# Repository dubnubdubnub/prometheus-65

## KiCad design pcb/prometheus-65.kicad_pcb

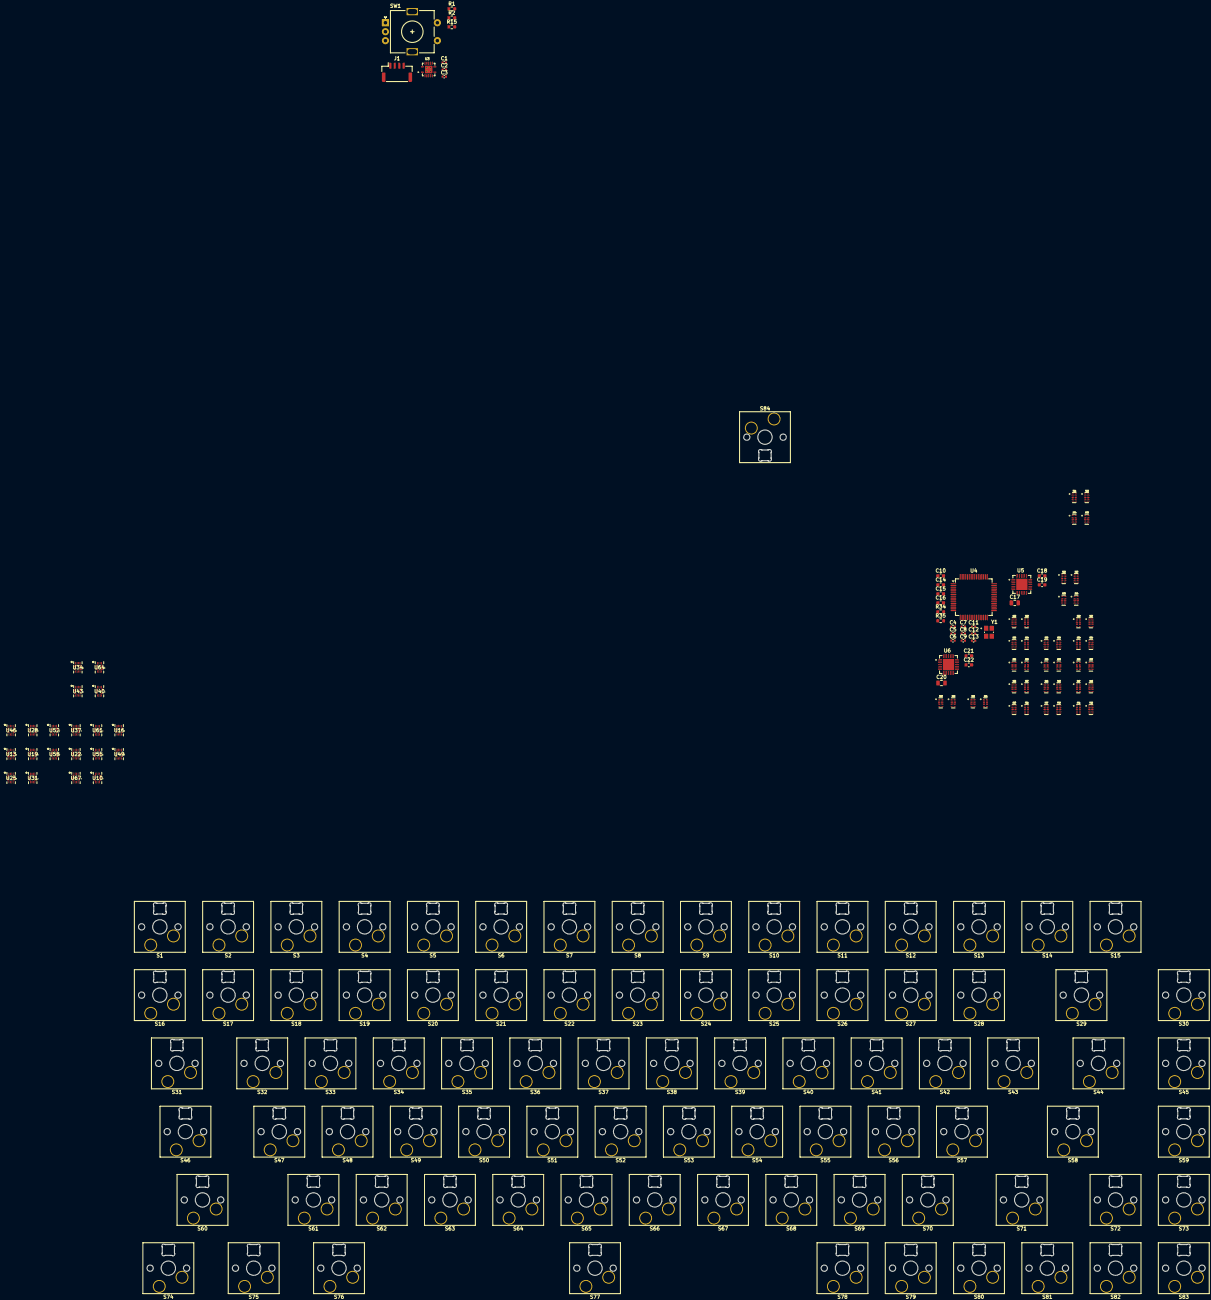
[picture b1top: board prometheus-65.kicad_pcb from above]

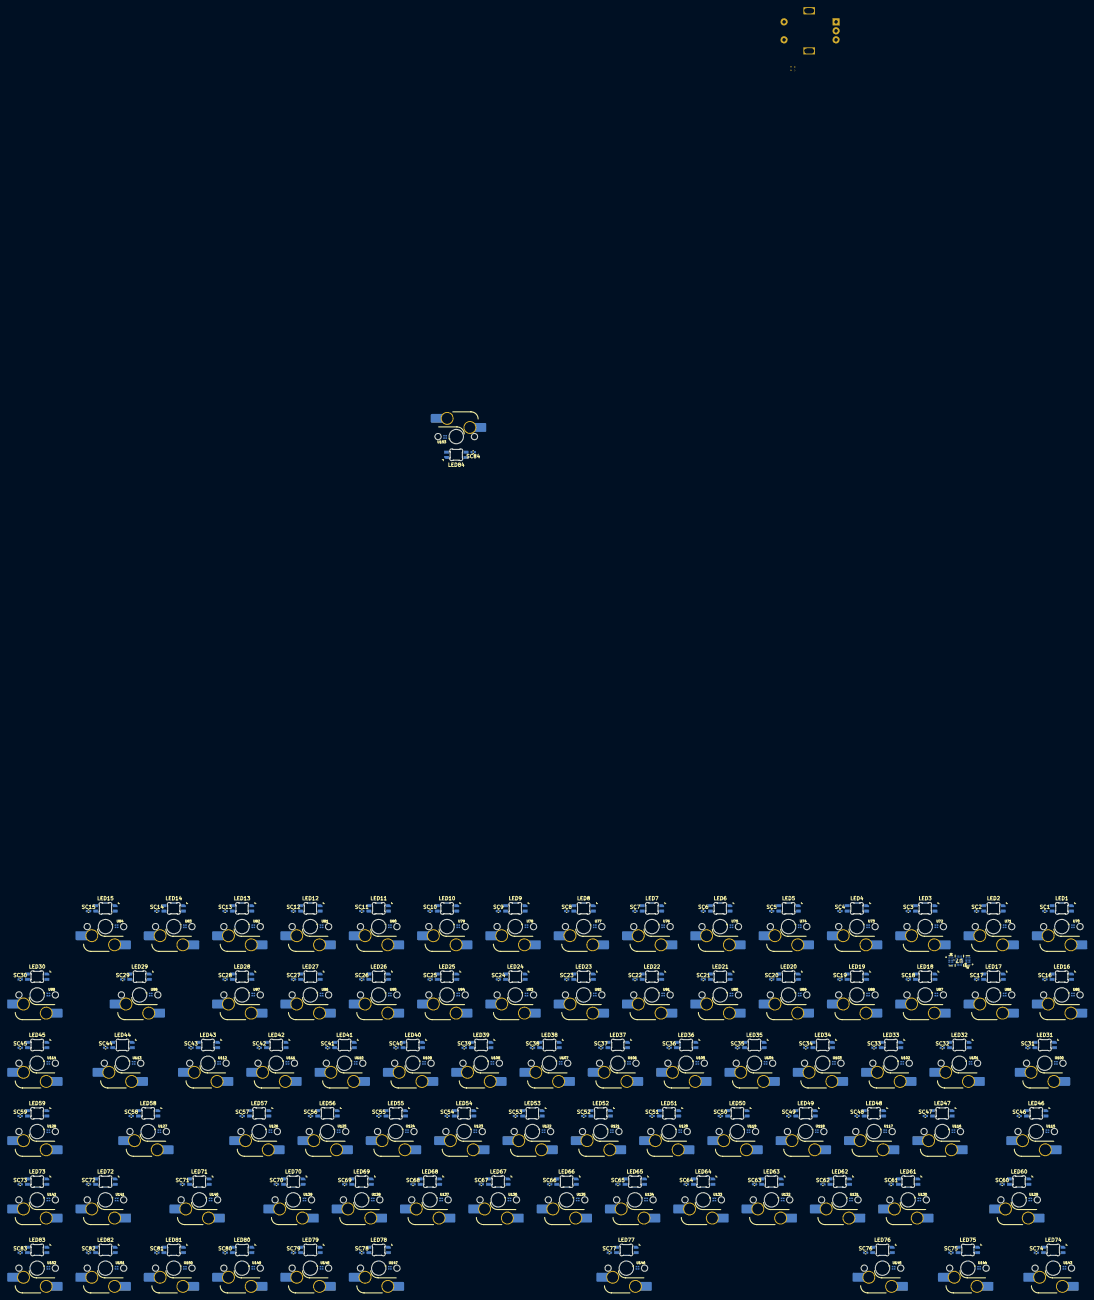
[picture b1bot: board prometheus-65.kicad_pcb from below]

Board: 6 copper layers, 433 parts (255 on the bottom side), 373 nets, no tracks yet.

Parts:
C1, C2, C3, C4, C5, C6, C7, C8, C9, C11: 100nF; C_0402_1005Metric
C10: 4.7uF; C_0603_1608Metric
C12, C13: 22pF; C_0402_1005Metric
C14, C15: 2.2uF; C_0603_1608Metric
C16, C19, C22: 1uF; C_0603_1608Metric
C17, C20: 47uF; C_0805_2012Metric
C18, C21: 10uF; C_0603_1608Metric
J1: Conn_01x04_Socket; JST_GH_SM04B-GHS-TB_1x04-1MP_P1.25mm_Horizontal
LED1, LED2, LED3, LED4, LED5, LED6, LED7, LED8, LED9, LED10, LED11, LED12, LED13, LED14, LED15, LED16, LED17, LED18, LED19, LED20, LED21, LED22, LED23, LED24, LED25, LED26, LED27, LED28, LED29, LED30, LED31, LED32, LED33, LED34, LED35, LED36, LED37, LED38, LED39, LED40, LED41, LED42, LED43, LED44, LED45, LED46, LED47, LED48, LED49, LED50, LED51, LED52, LED53, LED54, LED55, LED56, LED57, LED58, LED59, LED60, LED61, LED62, LED63, LED64, LED65, LED66, LED67, LED68, LED69, LED70, LED71, LED72, LED73, LED74, LED75, LED76, LED77, LED78, LED79, LED80, LED81, LED82, LED83, LED84: SK6812MINI-E; LED_6028R
R1, R2: 22Ω; R_0603_1608Metric
R15: 330Ω; R_0603_1608Metric
R34, R35: 10kΩ; R_0603_1608Metric
S1, S2, S3, S4, S5, S6, S7, S8, S9, S10, S11, S12, S13, S14, S15, S16, S17, S18, S19, S20, S21, S22, S23, S24, S25, S26, S27, S28, S29, S30, S31, S32, S33, S34, S35, S36, S37, S38, S39, S40, S41, S42, S43, S44, S45, S46, S47, S48, S49, S50, S51, S52, S53, S54, S55, S56, S57, S58, S59, S60, S61, S62, S63, S64, S65, S66, S67, S68, S69, S70, S71, S72, S73, S74, S75, S76, S77, S78, S79, S80, S81, S82, S83, S84: 1.00u; Hotswap_MX_Plated_1.00u
SC1, SC2, SC3, SC4, SC5, SC6, SC7, SC8, SC9, SC10, SC11, SC12, SC13, SC14, SC15, SC16, SC17, SC18, SC19, SC20, SC21, SC22, SC23, SC24, SC25, SC26, SC27, SC28, SC29, SC30, SC31, SC32, SC33, SC34, SC35, SC36, SC37, SC38, SC39, SC40, SC41, SC42, SC43, SC44, SC45, SC46, SC47, SC48, SC49, SC50, SC51, SC52, SC53, SC54, SC55, SC56, SC57, SC58, SC59, SC60, SC61, SC62, SC63, SC64, SC65, SC66, SC67, SC68, SC69, SC70, SC71, SC72, SC73, SC74, SC75, SC76, SC77, SC78, SC79, SC80, SC81, SC82, SC83, SC84: 100nF; C_0402_1005Metric
SW1: RotaryEncoder_Switch; RotaryEncoder_Alps_EC11E-Switch_Vertical_H20mm
U3: 74AHCT125; SN74AUC08RGYRG4
U4: STM32F405RGTx; LQFP-64_10x10mm_P0.5mm
U5, U6: TPS7A4700; TPS7A47000RGWT
U7, U10, U13, U16, U19, U22, U25, U28, U31, U34, U37, U40, U43, U46, U49, U52, U55, U58, U61, U64, U67: TMUX1109RSVR
U8, U9, U11, U12, U14, U15, U17, U18, U20, U21, U23, U24, U26, U27, U29, U30, U32, U33, U35, U36, U38, U39, U41, U42, U44, U45, U47, U48, U50, U51, U53, U54, U56, U57, U59, U60, U62, U63, U65, U66, U68, U69: TPD4E05U06DQAR
U70, U71, U72, U73, U74, U75, U76, U77, U78, U79, U80, U81, U82, U83, U84, U85, U86, U87, U88, U89, U90, U91, U92, U93, U94, U95, U96, U97, U98, U99, U100, U101, U102, U103, U104, U105, U106, U107, U108, U109, U110, U111, U112, U113, U114, U115, U116, U117, U118, U119, U120, U121, U122, U123, U124, U125, U126, U127, U128, U129, U130, U131, U132, U133, U134, U135, U136, U137, U138, U139, U140, U141, U142, U143, U144, U145, U146, U147, U148, U149, U150, U151, U152, U153: ALT025-14E
Y1: FA-238_16.0000MA20W-C

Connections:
+3.3VA: C1.2, C3.2, C9.2, C16.2, C20.1, U4.13 (VDDA), U6.1 (OUT), U6.3 (SENSE/FB), U6.20 (OUT), U70.2 (VCC), U71.2 (VCC), U72.2 (VCC), U73.2 (VCC), U74.2 (VCC), U75.2 (VCC), U76.2 (VCC), U77.2 (VCC), U78.2 (VCC), U79.2 (VCC), U80.2 (VCC), U81.2 (VCC), U82.2 (VCC), U83.2 (VCC), U84.2 (VCC), U85.2 (VCC), U86.2 (VCC), U87.2 (VCC), U88.2 (VCC), U89.2 (VCC), U90.2 (VCC), U91.2 (VCC), U92.2 (VCC), U93.2 (VCC), U94.2 (VCC), U95.2 (VCC), U96.2 (VCC), U97.2 (VCC), U98.2 (VCC), U99.2 (VCC), U100.2 (VCC), U101.2 (VCC), U102.2 (VCC), U103.2 (VCC), U104.2 (VCC), U105.2 (VCC), U106.2 (VCC), U107.2 (VCC), U108.2 (VCC), U109.2 (VCC), U110.2 (VCC), U111.2 (VCC), U112.2 (VCC), U113.2 (VCC), U114.2 (VCC), U115.2 (VCC), U116.2 (VCC), U117.2 (VCC), U118.2 (VCC), U119.2 (VCC), U120.2 (VCC), U121.2 (VCC), U122.2 (VCC), U123.2 (VCC), U124.2 (VCC), U125.2 (VCC), U126.2 (VCC), U127.2 (VCC), U128.2 (VCC), U129.2 (VCC), U130.2 (VCC), U131.2 (VCC), U132.2 (VCC), U133.2 (VCC), U134.2 (VCC), U135.2 (VCC), U136.2 (VCC), U137.2 (VCC), U138.2 (VCC), U139.2 (VCC), U140.2 (VCC), U141.2 (VCC), U142.2 (VCC), U143.2 (VCC), U144.2 (VCC), U145.2 (VCC), U146.2 (VCC), U147.2 (VCC), U148.2 (VCC), U149.2 (VCC), U150.2 (VCC), U151.2 (VCC), U152.2 (VCC), U153.2 (VCC)
+3.3VD: C4.2, C5.2, C6.2, C7.2, C8.2, C10.1, C17.1, R34.2, U4.1 (VBAT), U4.19 (VDD), U4.32 (VDD), U4.48 (VDD), U4.64 (VDD), U5.1 (OUT), U5.3 (SENSE/FB), U5.20 (OUT)
+5V: C18.2, C21.2, J1.1, SC1.1, SC2.1, SC3.1, SC4.1, SC5.1, SC6.1, SC7.1, SC8.1, SC9.1, SC10.1, SC11.1, SC12.1, SC13.1, SC14.1, SC15.1, SC16.1, SC17.1, SC18.1, SC19.1, SC20.1, SC21.1, SC22.1, SC23.1, SC24.1, SC25.1, SC26.1, SC27.1, SC28.1, SC29.1, SC30.1, SC31.1, SC32.1, SC33.1, SC34.1, SC35.1, SC36.1, SC37.1, SC38.1, SC39.1, SC40.1, SC41.1, SC42.1, SC43.1, SC44.1, SC45.1, SC46.1, SC47.1, SC48.1, SC49.1, SC50.1, SC51.1, SC52.1, SC53.1, SC54.1, SC55.1, SC56.1, SC57.1, SC58.1, SC59.1, SC60.1, SC61.1, SC62.1, SC63.1, SC64.1, SC65.1, SC66.1, SC67.1, SC68.1, SC69.1, SC70.1, SC71.1, SC72.1, SC73.1, SC74.1, SC75.1, SC76.1, SC77.1, SC78.1, SC79.1, SC80.1, SC81.1, SC82.1, SC83.1, SC84.1, U3.14 (VCC), U5.13 (EN), U5.15 (IN), U5.16 (IN), U6.13 (EN), U6.15 (IN), U6.16 (IN)
/Key_1/DOUT: LED1.2 (DOUT), LED2.3 (DIN)
/Key_1/OUT+: S1.1, U7.2 (S1A), U8.1 (D1+), U70.1 (OUT+)
/Key_1/OUT-: U7.11 (S1B), U8.2 (D1-), U70.3 (OUT-)
/Key_2/DOUT: LED2.2 (DOUT), LED3.3 (DIN)
/Key_2/OUT+: S2.1, U7.3 (S2A), U8.4 (D2+), U71.1 (OUT+)
/Key_2/OUT-: U7.10 (S2B), U8.5 (D2-), U71.3 (OUT-)
/Key_3/DOUT: LED3.2 (DOUT), LED4.3 (DIN)
/Key_3/OUT+: S3.1, U7.4 (S3A), U9.1 (D1+), U72.1 (OUT+)
/Key_3/OUT-: U7.9 (S3B), U9.2 (D1-), U72.3 (OUT-)
/Key_4/DOUT: LED4.2 (DOUT), LED5.3 (DIN)
/Key_4/OUT+: S4.1, U7.5 (S4A), U9.4 (D2+), U73.1 (OUT+)
/Key_4/OUT-: U7.8 (S4B), U9.5 (D2-), U73.3 (OUT-)
/Key_5/OUT+: S5.1, U10.2 (S1A), U11.1 (D1+), U74.1 (OUT+)
/Key_5/OUT-: U10.11 (S1B), U11.2 (D1-), U74.3 (OUT-)
/Key_6/OUT+: S6.1, U10.3 (S2A), U11.4 (D2+), U75.1 (OUT+)
/Key_6/OUT-: U10.10 (S2B), U11.5 (D2-), U75.3 (OUT-)
/Key_7/OUT+: S7.1, U10.4 (S3A), U12.1 (D1+), U76.1 (OUT+)
/Key_7/OUT-: U10.9 (S3B), U12.2 (D1-), U76.3 (OUT-)
/Key_8/DOUT: LED8.2 (DOUT), LED9.3 (DIN)
/Key_8/OUT+: S8.1, U10.5 (S4A), U12.4 (D2+), U77.1 (OUT+)
/Key_8/OUT-: U10.8 (S4B), U12.5 (D2-), U77.3 (OUT-)
/Key_9/OUT+: S9.1, U13.2 (S1A), U14.1 (D1+), U78.1 (OUT+)
/Key_9/OUT-: U13.11 (S1B), U14.2 (D1-), U78.3 (OUT-)
/Key_10/DIN: LED9.2 (DOUT), LED10.3 (DIN)
/Key_10/DOUT: LED10.2 (DOUT), LED11.3 (DIN)
/Key_10/OUT+: S10.1, U13.3 (S2A), U14.4 (D2+), U79.1 (OUT+)
/Key_10/OUT-: U13.10 (S2B), U14.5 (D2-), U79.3 (OUT-)
/Key_11/DOUT: LED11.2 (DOUT), LED12.3 (DIN)
/Key_11/OUT+: S11.1, U13.4 (S3A), U15.1 (D1+), U80.1 (OUT+)
/Key_11/OUT-: U13.9 (S3B), U15.2 (D1-), U80.3 (OUT-)
/Key_12/DOUT: LED12.2 (DOUT), LED13.3 (DIN)
/Key_12/OUT+: S12.1, U13.5 (S4A), U15.4 (D2+), U81.1 (OUT+)
/Key_12/OUT-: U13.8 (S4B), U15.5 (D2-), U81.3 (OUT-)
/Key_13/DOUT: LED13.2 (DOUT), LED14.3 (DIN)
/Key_13/OUT+: S13.1, U16.2 (S1A), U17.1 (D1+), U82.1 (OUT+)
/Key_13/OUT-: U16.11 (S1B), U17.2 (D1-), U82.3 (OUT-)
/Key_14/DOUT: LED14.2 (DOUT), LED15.3 (DIN)
/Key_14/OUT+: S14.1, U16.3 (S2A), U17.4 (D2+), U83.1 (OUT+)
/Key_14/OUT-: U16.10 (S2B), U17.5 (D2-), U83.3 (OUT-)
/Key_15/DOUT: LED15.2 (DOUT), LED16.3 (DIN)
/Key_15/OUT+: S15.1, U16.4 (S3A), U18.1 (D1+), U84.1 (OUT+)
/Key_15/OUT-: U16.9 (S3B), U18.2 (D1-), U84.3 (OUT-)
/Key_16/DOUT: LED16.2 (DOUT), LED17.3 (DIN)
/Key_16/OUT+: S16.1, U16.5 (S4A), U18.4 (D2+), U85.1 (OUT+)
/Key_16/OUT-: U16.8 (S4B), U18.5 (D2-), U85.3 (OUT-)
/Key_17/DOUT: LED17.2 (DOUT), LED18.3 (DIN)
/Key_17/OUT+: S17.1, U19.2 (S1A), U20.1 (D1+), U86.1 (OUT+)
/Key_17/OUT-: U19.11 (S1B), U20.2 (D1-), U86.3 (OUT-)
/Key_18/DOUT: LED18.2 (DOUT), LED19.3 (DIN)
/Key_18/OUT+: S18.1, U19.3 (S2A), U20.4 (D2+), U87.1 (OUT+)
/Key_18/OUT-: U19.10 (S2B), U20.5 (D2-), U87.3 (OUT-)
/Key_19/DOUT: LED19.2 (DOUT), LED20.3 (DIN)
/Key_19/OUT+: S19.1, U19.4 (S3A), U21.1 (D1+), U88.1 (OUT+)
/Key_19/OUT-: U19.9 (S3B), U21.2 (D1-), U88.3 (OUT-)
/Key_20/DOUT: LED20.2 (DOUT), LED21.3 (DIN)
/Key_20/OUT+: S20.1, U19.5 (S4A), U21.4 (D2+), U89.1 (OUT+)
/Key_20/OUT-: U19.8 (S4B), U21.5 (D2-), U89.3 (OUT-)
/Key_21/DOUT: LED21.2 (DOUT), LED22.3 (DIN)
/Key_21/OUT+: S21.1, U22.2 (S1A), U23.1 (D1+), U90.1 (OUT+)
/Key_21/OUT-: U22.11 (S1B), U23.2 (D1-), U90.3 (OUT-)
/Key_22/DOUT: LED22.2 (DOUT), LED23.3 (DIN)
/Key_22/OUT+: S22.1, U22.3 (S2A), U23.4 (D2+), U91.1 (OUT+)
/Key_22/OUT-: U22.10 (S2B), U23.5 (D2-), U91.3 (OUT-)
/Key_23/DOUT: LED23.2 (DOUT), LED24.3 (DIN)
/Key_23/OUT+: S23.1, U22.4 (S3A), U24.1 (D1+), U92.1 (OUT+)
/Key_23/OUT-: U22.9 (S3B), U24.2 (D1-), U92.3 (OUT-)
/Key_24/DOUT: LED24.2 (DOUT), LED25.3 (DIN)
/Key_24/OUT+: S24.1, U22.5 (S4A), U24.4 (D2+), U93.1 (OUT+)
/Key_24/OUT-: U22.8 (S4B), U24.5 (D2-), U93.3 (OUT-)
/Key_25/DOUT: LED25.2 (DOUT), LED26.3 (DIN)
/Key_25/OUT+: S25.1, U25.2 (S1A), U26.1 (D1+), U94.1 (OUT+)
/Key_25/OUT-: U25.11 (S1B), U26.2 (D1-), U94.3 (OUT-)
/Key_26/DOUT: LED26.2 (DOUT), LED27.3 (DIN)
/Key_26/OUT+: S26.1, U25.3 (S2A), U26.4 (D2+), U95.1 (OUT+)
/Key_26/OUT-: U25.10 (S2B), U26.5 (D2-), U95.3 (OUT-)
/Key_27/DOUT: LED27.2 (DOUT), LED28.3 (DIN)
/Key_27/OUT+: S27.1, U25.4 (S3A), U27.1 (D1+), U96.1 (OUT+)
/Key_27/OUT-: U25.9 (S3B), U27.2 (D1-), U96.3 (OUT-)
/Key_28/DOUT: LED28.2 (DOUT), LED29.3 (DIN)
/Key_28/OUT+: S28.1, U25.5 (S4A), U27.4 (D2+), U97.1 (OUT+)
/Key_28/OUT-: U25.8 (S4B), U27.5 (D2-), U97.3 (OUT-)
/Key_29/DOUT: LED29.2 (DOUT), LED30.3 (DIN)
/Key_29/OUT+: S29.1, U28.2 (S1A), U29.1 (D1+), U98.1 (OUT+)
/Key_29/OUT-: U28.11 (S1B), U29.2 (D1-), U98.3 (OUT-)
/Key_30/DOUT: LED30.2 (DOUT), LED31.3 (DIN)
/Key_30/OUT+: S30.1, U28.3 (S2A), U29.4 (D2+), U99.1 (OUT+)
/Key_30/OUT-: U28.10 (S2B), U29.5 (D2-), U99.3 (OUT-)
/Key_31/DOUT: LED31.2 (DOUT), LED32.3 (DIN)
/Key_31/OUT+: S31.1, U28.4 (S3A), U30.1 (D1+), U100.1 (OUT+)
/Key_31/OUT-: U28.9 (S3B), U30.2 (D1-), U100.3 (OUT-)
/Key_32/DOUT: LED32.2 (DOUT), LED33.3 (DIN)
/Key_32/OUT+: S32.1, U28.5 (S4A), U30.4 (D2+), U101.1 (OUT+)
/Key_32/OUT-: U28.8 (S4B), U30.5 (D2-), U101.3 (OUT-)
/Key_33/DOUT: LED33.2 (DOUT), LED34.3 (DIN)
/Key_33/OUT+: S33.1, U31.2 (S1A), U32.1 (D1+), U102.1 (OUT+)
/Key_33/OUT-: U31.11 (S1B), U32.2 (D1-), U102.3 (OUT-)
/Key_34/DOUT: LED34.2 (DOUT), LED35.3 (DIN)
/Key_34/OUT+: S34.1, U31.3 (S2A), U32.4 (D2+), U103.1 (OUT+)
/Key_34/OUT-: U31.10 (S2B), U32.5 (D2-), U103.3 (OUT-)
/Key_35/DOUT: LED35.2 (DOUT), LED36.3 (DIN)
/Key_35/OUT+: S35.1, U31.4 (S3A), U33.1 (D1+), U104.1 (OUT+)
/Key_35/OUT-: U31.9 (S3B), U33.2 (D1-), U104.3 (OUT-)
/Key_36/DOUT: LED36.2 (DOUT), LED37.3 (DIN)
/Key_36/OUT+: S36.1, U31.5 (S4A), U33.4 (D2+), U105.1 (OUT+)
/Key_36/OUT-: U31.8 (S4B), U33.5 (D2-), U105.3 (OUT-)
/Key_37/DOUT: LED37.2 (DOUT), LED38.3 (DIN)
/Key_37/OUT+: S37.1, U34.2 (S1A), U35.1 (D1+), U106.1 (OUT+)
/Key_37/OUT-: U34.11 (S1B), U35.2 (D1-), U106.3 (OUT-)
/Key_38/DOUT: LED38.2 (DOUT), LED39.3 (DIN)
/Key_38/OUT+: S38.1, U34.3 (S2A), U35.4 (D2+), U107.1 (OUT+)
/Key_38/OUT-: U34.10 (S2B), U35.5 (D2-), U107.3 (OUT-)
/Key_39/DOUT: LED39.2 (DOUT), LED40.3 (DIN)
/Key_39/OUT+: S39.1, U34.4 (S3A), U36.1 (D1+), U108.1 (OUT+)
/Key_39/OUT-: U34.9 (S3B), U36.2 (D1-), U108.3 (OUT-)
/Key_40/DOUT: LED40.2 (DOUT), LED41.3 (DIN)
/Key_40/OUT+: S40.1, U34.5 (S4A), U36.4 (D2+), U109.1 (OUT+)
/Key_40/OUT-: U34.8 (S4B), U36.5 (D2-), U109.3 (OUT-)
/Key_41/DOUT: LED41.2 (DOUT), LED42.3 (DIN)
/Key_41/OUT+: S41.1, U37.2 (S1A), U38.1 (D1+), U110.1 (OUT+)
/Key_41/OUT-: U37.11 (S1B), U38.2 (D1-), U110.3 (OUT-)
/Key_42/DOUT: LED42.2 (DOUT), LED43.3 (DIN)
/Key_42/OUT+: S42.1, U37.3 (S2A), U38.4 (D2+), U111.1 (OUT+)
/Key_42/OUT-: U37.10 (S2B), U38.5 (D2-), U111.3 (OUT-)
/Key_43/DOUT: LED43.2 (DOUT), LED44.3 (DIN)
/Key_43/OUT+: S43.1, U37.4 (S3A), U39.1 (D1+), U112.1 (OUT+)
/Key_43/OUT-: U37.9 (S3B), U39.2 (D1-), U112.3 (OUT-)
/Key_44/DOUT: LED44.2 (DOUT), LED45.3 (DIN)
/Key_44/OUT+: S44.1, U37.5 (S4A), U39.4 (D2+), U113.1 (OUT+)
/Key_44/OUT-: U37.8 (S4B), U39.5 (D2-), U113.3 (OUT-)
/Key_45/DOUT: LED45.2 (DOUT), LED46.3 (DIN)
/Key_45/OUT+: S45.1, U40.2 (S1A), U41.1 (D1+), U114.1 (OUT+)
/Key_45/OUT-: U40.11 (S1B), U41.2 (D1-), U114.3 (OUT-)
/Key_46/DOUT: LED46.2 (DOUT), LED47.3 (DIN)
/Key_46/OUT+: S46.1, U40.3 (S2A), U41.4 (D2+), U115.1 (OUT+)
/Key_46/OUT-: U40.10 (S2B), U41.5 (D2-), U115.3 (OUT-)
/Key_47/DOUT: LED47.2 (DOUT), LED48.3 (DIN)
/Key_47/OUT+: S47.1, U40.4 (S3A), U42.1 (D1+), U116.1 (OUT+)
/Key_47/OUT-: U40.9 (S3B), U42.2 (D1-), U116.3 (OUT-)
/Key_48/DOUT: LED48.2 (DOUT), LED49.3 (DIN)
/Key_48/OUT+: S48.1, U40.5 (S4A), U42.4 (D2+), U117.1 (OUT+)
/Key_48/OUT-: U40.8 (S4B), U42.5 (D2-), U117.3 (OUT-)
/Key_49/DOUT: LED49.2 (DOUT), LED50.3 (DIN)
/Key_49/OUT+: S49.1, U43.2 (S1A), U44.1 (D1+), U118.1 (OUT+)
/Key_49/OUT-: U43.11 (S1B), U44.2 (D1-), U118.3 (OUT-)
/Key_50/DOUT: LED50.2 (DOUT), LED51.3 (DIN)
/Key_50/OUT+: S50.1, U43.3 (S2A), U44.4 (D2+), U119.1 (OUT+)
/Key_50/OUT-: U43.10 (S2B), U44.5 (D2-), U119.3 (OUT-)
/Key_51/DOUT: LED51.2 (DOUT), LED52.3 (DIN)
/Key_51/OUT+: S51.1, U43.4 (S3A), U45.1 (D1+), U120.1 (OUT+)
/Key_51/OUT-: U43.9 (S3B), U45.2 (D1-), U120.3 (OUT-)
/Key_52/DOUT: LED52.2 (DOUT), LED53.3 (DIN)
/Key_52/OUT+: S52.1, U43.5 (S4A), U45.4 (D2+), U121.1 (OUT+)
/Key_52/OUT-: U43.8 (S4B), U45.5 (D2-), U121.3 (OUT-)
/Key_53/DOUT: LED53.2 (DOUT), LED54.3 (DIN)
/Key_53/OUT+: S53.1, U46.2 (S1A), U47.1 (D1+), U122.1 (OUT+)
/Key_53/OUT-: U46.11 (S1B), U47.2 (D1-), U122.3 (OUT-)
/Key_54/DOUT: LED54.2 (DOUT), LED55.3 (DIN)
/Key_54/OUT+: S54.1, U46.3 (S2A), U47.4 (D2+), U123.1 (OUT+)
/Key_54/OUT-: U46.10 (S2B), U47.5 (D2-), U123.3 (OUT-)
/Key_55/DOUT: LED55.2 (DOUT), LED56.3 (DIN)
/Key_55/OUT+: S55.1, U46.4 (S3A), U48.1 (D1+), U124.1 (OUT+)
/Key_55/OUT-: U46.9 (S3B), U48.2 (D1-), U124.3 (OUT-)
/Key_56/DOUT: LED56.2 (DOUT), LED57.3 (DIN)
/Key_56/OUT+: S56.1, U46.5 (S4A), U48.4 (D2+), U125.1 (OUT+)
/Key_56/OUT-: U46.8 (S4B), U48.5 (D2-), U125.3 (OUT-)
/Key_57/DOUT: LED57.2 (DOUT), LED58.3 (DIN)
/Key_57/OUT+: S57.1, U49.2 (S1A), U50.1 (D1+), U126.1 (OUT+)
/Key_57/OUT-: U49.11 (S1B), U50.2 (D1-), U126.3 (OUT-)
/Key_58/DOUT: LED58.2 (DOUT), LED59.3 (DIN)
/Key_58/OUT+: S58.1, U49.3 (S2A), U50.4 (D2+), U127.1 (OUT+)
/Key_58/OUT-: U49.10 (S2B), U50.5 (D2-), U127.3 (OUT-)
/Key_59/DOUT: LED59.2 (DOUT), LED60.3 (DIN)
/Key_59/OUT+: S59.1, U49.4 (S3A), U51.1 (D1+), U128.1 (OUT+)
/Key_59/OUT-: U49.9 (S3B), U51.2 (D1-), U128.3 (OUT-)
/Key_60/DOUT: LED60.2 (DOUT), LED61.3 (DIN)
/Key_60/OUT+: S60.1, U49.5 (S4A), U51.4 (D2+), U129.1 (OUT+)
/Key_60/OUT-: U49.8 (S4B), U51.5 (D2-), U129.3 (OUT-)
/Key_61/DOUT: LED61.2 (DOUT), LED62.3 (DIN)
/Key_61/OUT+: S61.1, U52.2 (S1A), U53.1 (D1+), U130.1 (OUT+)
/Key_61/OUT-: U52.11 (S1B), U53.2 (D1-), U130.3 (OUT-)
/Key_62/DOUT: LED62.2 (DOUT), LED63.3 (DIN)
/Key_62/OUT+: S62.1, U52.3 (S2A), U53.4 (D2+), U131.1 (OUT+)
/Key_62/OUT-: U52.10 (S2B), U53.5 (D2-), U131.3 (OUT-)
/Key_63/DOUT: LED63.2 (DOUT), LED64.3 (DIN)
/Key_63/OUT+: S63.1, U52.4 (S3A), U54.1 (D1+), U132.1 (OUT+)
/Key_63/OUT-: U52.9 (S3B), U54.2 (D1-), U132.3 (OUT-)
/Key_64/DOUT: LED64.2 (DOUT), LED65.3 (DIN)
/Key_64/OUT+: S64.1, U52.5 (S4A), U54.4 (D2+), U133.1 (OUT+)
/Key_64/OUT-: U52.8 (S4B), U54.5 (D2-), U133.3 (OUT-)
/Key_65/DOUT: LED65.2 (DOUT), LED66.3 (DIN)
/Key_65/OUT+: S65.1, U55.2 (S1A), U56.1 (D1+), U134.1 (OUT+)
/Key_65/OUT-: U55.11 (S1B), U56.2 (D1-), U134.3 (OUT-)
/Key_66/DOUT: LED66.2 (DOUT), LED67.3 (DIN)
/Key_66/OUT+: S66.1, U55.3 (S2A), U56.4 (D2+), U135.1 (OUT+)
/Key_66/OUT-: U55.10 (S2B), U56.5 (D2-), U135.3 (OUT-)
/Key_67/DOUT: LED67.2 (DOUT), LED68.3 (DIN)
/Key_67/OUT+: S67.1, U55.4 (S3A), U57.1 (D1+), U136.1 (OUT+)
/Key_67/OUT-: U55.9 (S3B), U57.2 (D1-), U136.3 (OUT-)
/Key_68/DOUT: LED68.2 (DOUT), LED69.3 (DIN)
/Key_68/OUT+: S68.1, U55.5 (S4A), U57.4 (D2+), U137.1 (OUT+)
/Key_68/OUT-: U55.8 (S4B), U57.5 (D2-), U137.3 (OUT-)
/Key_69/DOUT: LED69.2 (DOUT), LED70.3 (DIN)
/Key_69/OUT+: S69.1, U58.2 (S1A), U59.1 (D1+), U138.1 (OUT+)
/Key_69/OUT-: U58.11 (S1B), U59.2 (D1-), U138.3 (OUT-)
/Key_70/DOUT: LED70.2 (DOUT), LED71.3 (DIN)
/Key_70/OUT+: S70.1, U58.3 (S2A), U59.4 (D2+), U139.1 (OUT+)
/Key_70/OUT-: U58.10 (S2B), U59.5 (D2-), U139.3 (OUT-)
/Key_71/DOUT: LED71.2 (DOUT), LED72.3 (DIN)
/Key_71/OUT+: S71.1, U58.4 (S3A), U60.1 (D1+), U140.1 (OUT+)
/Key_71/OUT-: U58.9 (S3B), U60.2 (D1-), U140.3 (OUT-)
/Key_72/DOUT: LED72.2 (DOUT), LED73.3 (DIN)
/Key_72/OUT+: S72.1, U58.5 (S4A), U60.4 (D2+), U141.1 (OUT+)
/Key_72/OUT-: U58.8 (S4B), U60.5 (D2-), U141.3 (OUT-)
/Key_73/DOUT: LED73.2 (DOUT), LED74.3 (DIN)
/Key_73/OUT+: S73.1, U61.2 (S1A), U62.1 (D1+), U142.1 (OUT+)
/Key_73/OUT-: U61.11 (S1B), U62.2 (D1-), U142.3 (OUT-)
/Key_74/DOUT: LED74.2 (DOUT), LED75.3 (DIN)
/Key_74/OUT+: S74.1, U61.3 (S2A), U62.4 (D2+), U143.1 (OUT+)
/Key_74/OUT-: U61.10 (S2B), U62.5 (D2-), U143.3 (OUT-)
/Key_75/DOUT: LED75.2 (DOUT), LED76.3 (DIN)
/Key_75/OUT+: S75.1, U61.4 (S3A), U63.1 (D1+), U144.1 (OUT+)
/Key_75/OUT-: U61.9 (S3B), U63.2 (D1-), U144.3 (OUT-)
/Key_76/DOUT: LED76.2 (DOUT), LED77.3 (DIN)
/Key_76/OUT+: S76.1, U61.5 (S4A), U63.4 (D2+), U145.1 (OUT+)
/Key_76/OUT-: U61.8 (S4B), U63.5 (D2-), U145.3 (OUT-)
/Key_77/DOUT: LED77.2 (DOUT), LED78.3 (DIN)
/Key_77/OUT+: S77.1, U64.2 (S1A), U65.1 (D1+), U146.1 (OUT+)
/Key_77/OUT-: U64.11 (S1B), U65.2 (D1-), U146.3 (OUT-)
/Key_78/DOUT: LED78.2 (DOUT), LED79.3 (DIN)
/Key_78/OUT+: S78.1, U64.3 (S2A), U65.4 (D2+), U147.1 (OUT+)
/Key_78/OUT-: U64.10 (S2B), U65.5 (D2-), U147.3 (OUT-)
/Key_79/DOUT: LED79.2 (DOUT), LED80.3 (DIN)
/Key_79/OUT+: S79.1, U64.4 (S3A), U66.1 (D1+), U148.1 (OUT+)
/Key_79/OUT-: U64.9 (S3B), U66.2 (D1-), U148.3 (OUT-)
/Key_80/DOUT: LED80.2 (DOUT), LED81.3 (DIN)
/Key_80/OUT+: S80.1, U64.5 (S4A), U66.4 (D2+), U149.1 (OUT+)
/Key_80/OUT-: U64.8 (S4B), U66.5 (D2-), U149.3 (OUT-)
/Key_81/DOUT: LED81.2 (DOUT), LED82.3 (DIN)
/Key_81/OUT+: S81.1, U67.2 (S1A), U68.1 (D1+), U150.1 (OUT+)
/Key_81/OUT-: U67.11 (S1B), U68.2 (D1-), U150.3 (OUT-)
/Key_82/DOUT: LED82.2 (DOUT), LED83.3 (DIN)
/Key_82/OUT+: S82.1, U67.3 (S2A), U68.4 (D2+), U151.1 (OUT+)
/Key_82/OUT-: U67.10 (S2B), U68.5 (D2-), U151.3 (OUT-)
/Key_83/DOUT: LED83.2 (DOUT), LED84.3 (DIN)
/Key_83/OUT+: S83.1, U67.4 (S3A), U69.1 (D1+), U152.1 (OUT+)
/Key_83/OUT-: U67.9 (S3B), U69.2 (D1-), U152.3 (OUT-)
/Key_84/DOUT: LED84.2 (DOUT), R15.2
/Key_84/OUT+: S84.1, U67.5 (S4A), U69.4 (D2+), U153.1 (OUT+)
/Key_84/OUT-: U67.8 (S4B), U69.5 (D2-), U153.3 (OUT-)
/Mux_1/MUX_DA: U7.6 (DA), U28.6 (DA), U49.6 (DA)
/Mux_1/MUX_DB: U7.7 (DB), U28.7 (DB), U49.7 (DB)
/Mux_1/MUX_EN: U4.10 (PC2), U7.16 (EN), U10.16 (EN), U13.16 (EN), U16.16 (EN), U19.16 (EN), U22.16 (EN), U25.16 (EN)
/Mux_10/MUX_DA: U13.6 (DA), U34.6 (DA), U55.6 (DA)
/Mux_10/MUX_DB: U13.7 (DB), U34.7 (DB), U55.7 (DB)
/Mux_10/MUX_EN: U4.11 (PC3), U28.16 (EN), U31.16 (EN), U34.16 (EN), U37.16 (EN), U40.16 (EN), U43.16 (EN), U46.16 (EN)
/Mux_11/MUX_DA: U16.6 (DA), U37.6 (DA), U58.6 (DA)
/Mux_11/MUX_DB: U16.7 (DB), U37.7 (DB), U58.7 (DB)
/Mux_12/MUX_DA: U19.6 (DA), U40.6 (DA), U61.6 (DA)
/Mux_12/MUX_DB: U19.7 (DB), U40.7 (DB), U61.7 (DB)
/Mux_13/MUX_DA: U22.6 (DA), U43.6 (DA), U64.6 (DA)
/Mux_13/MUX_DB: U22.7 (DB), U43.7 (DB), U64.7 (DB)
/Mux_14/MUX_DA: U25.6 (DA), U46.6 (DA), U67.6 (DA)
/Mux_14/MUX_DB: U25.7 (DB), U46.7 (DB), U67.7 (DB)
/Mux_15/MUX_EN: U4.24 (PC4), U49.16 (EN), U52.16 (EN), U55.16 (EN), U58.16 (EN), U61.16 (EN), U64.16 (EN), U67.16 (EN)
/Mux_16/MUX_DA: U10.6 (DA), U31.6 (DA), U52.6 (DA)
/Mux_16/MUX_DB: U10.7 (DB), U31.7 (DB), U52.7 (DB)
/STM32F405RGT6/ENC_CH1: SW1.A, U4.41 (PA8)
/STM32F405RGT6/ENC_CH2: SW1.B, U4.42 (PA9)
/STM32F405RGT6/ENC_SIG: SW1.S1, U4.43 (PA10)
/STM32F405RGT6/LED_DOUT: U3.2, U4.57 (PB5)
D+: R2.2, U4.36 (PB15)
D-: R1.2, U4.35 (PB14)
GND: C1.1, C2.1, C3.1, C4.1, C5.1, C6.1, C7.1, C8.1, C9.1, C10.2, C11.1, C12.1, C13.1, C14.1, C15.1, C16.1, C17.2, C18.1, C19.1, C20.2, C21.1, C22.1, J1.4, LED1.4 (VSS), LED2.4 (VSS), LED3.4 (VSS), LED4.4 (VSS), LED5.4 (VSS), LED6.4 (VSS), LED7.4 (VSS), LED8.4 (VSS), LED9.4 (VSS), LED10.4 (VSS), LED11.4 (VSS), LED12.4 (VSS), LED13.4 (VSS), LED14.4 (VSS), LED15.4 (VSS), LED16.4 (VSS), LED17.4 (VSS), LED18.4 (VSS), LED19.4 (VSS), LED20.4 (VSS), LED21.4 (VSS), LED22.4 (VSS), LED23.4 (VSS), LED24.4 (VSS), LED25.4 (VSS), LED26.4 (VSS), LED27.4 (VSS), LED28.4 (VSS), LED29.4 (VSS), LED30.4 (VSS), LED31.4 (VSS), LED32.4 (VSS), LED33.4 (VSS), LED34.4 (VSS), LED35.4 (VSS), LED36.4 (VSS), LED37.4 (VSS), LED38.4 (VSS), LED39.4 (VSS), LED40.4 (VSS), LED41.4 (VSS), LED42.4 (VSS), LED43.4 (VSS), LED44.4 (VSS), LED45.4 (VSS), LED46.4 (VSS), LED47.4 (VSS), LED48.4 (VSS), LED49.4 (VSS), LED50.4 (VSS), LED51.4 (VSS), LED52.4 (VSS), LED53.4 (VSS), LED54.4 (VSS), LED55.4 (VSS), LED56.4 (VSS), LED57.4 (VSS), LED58.4 (VSS), LED59.4 (VSS), LED60.4 (VSS), LED61.4 (VSS), LED62.4 (VSS), LED63.4 (VSS), LED64.4 (VSS), LED65.4 (VSS), LED66.4 (VSS), LED67.4 (VSS), LED68.4 (VSS), LED69.4 (VSS), LED70.4 (VSS), LED71.4 (VSS), LED72.4 (VSS), LED73.4 (VSS), LED74.4 (VSS), LED75.4 (VSS), LED76.4 (VSS), LED77.4 (VSS), LED78.4 (VSS), LED79.4 (VSS), LED80.4 (VSS), LED81.4 (VSS), LED82.4 (VSS), LED83.4 (VSS), LED84.4 (VSS), R35.1, S1.2, S2.2, S3.2, S4.2, S5.2, S6.2, S7.2, S8.2, S9.2, S10.2, S11.2, S12.2, S13.2, S14.2, S15.2, S16.2, S17.2, S18.2, S19.2, S20.2, S21.2, S22.2, S23.2, S24.2, S25.2, S26.2, S27.2, S28.2, S29.2, S30.2, S31.2, S32.2, S33.2, S34.2, S35.2, S36.2, S37.2, S38.2, S39.2, S40.2, S41.2, S42.2, S43.2, S44.2, S45.2, S46.2, S47.2, S48.2, S49.2, S50.2, S51.2, S52.2, S53.2, S54.2, S55.2, S56.2, S57.2, S58.2, S59.2, S60.2, S61.2, S62.2, S63.2, S64.2, S65.2, S66.2, S67.2, S68.2, S69.2, S70.2, S71.2, S72.2, S73.2, S74.2, S75.2, S76.2, S77.2, S78.2, S79.2, S80.2, S81.2, S82.2, S83.2, S84.2, SW1.C, SW1.S2, U3.1, U3.4, U3.5, U3.7 (GND), U3.9, U3.10, U3.12, U3.13, U4.12 (VSSA), U4.18 (VSS), U4.63 (VSS), U5.7 (GND), U5.8 (1P6V), U5.11 (0P2V), U5.12 (0P1V), U5.21 (TP), U6.7 (GND), U6.8 (1P6V), U6.11 (0P2V), U6.12 (0P1V), U6.21 (TP), U7.1 (VSS), U7.13 (GND), U8.3 (GND), U8.8 (GND), U9.3 (GND), U9.8 (GND), U10.1 (VSS), U10.13 (GND), U11.3 (GND), U11.8 (GND), U12.3 (GND), U12.8 (GND), U13.1 (VSS), U13.13 (GND), U14.3 (GND), U14.8 (GND), U15.3 (GND), U15.8 (GND), U16.1 (VSS), U16.13 (GND), U17.3 (GND), U17.8 (GND), U18.3 (GND), U18.8 (GND), U19.1 (VSS), U19.13 (GND), U20.3 (GND), U20.8 (GND), U21.3 (GND), U21.8 (GND), U22.1 (VSS), U22.13 (GND), U23.3 (GND), U23.8 (GND), U24.3 (GND), U24.8 (GND), U25.1 (VSS), U25.13 (GND), U26.3 (GND), U26.8 (GND), U27.3 (GND), U27.8 (GND), U28.1 (VSS), U28.13 (GND), U29.3 (GND), U29.8 (GND), U30.3 (GND), U30.8 (GND), U31.1 (VSS), U31.13 (GND), U32.3 (GND), U32.8 (GND), U33.3 (GND), U33.8 (GND), U34.1 (VSS), U34.13 (GND), U35.3 (GND), U35.8 (GND), U36.3 (GND), U36.8 (GND), U37.1 (VSS), U37.13 (GND), U38.3 (GND), U38.8 (GND), U39.3 (GND), U39.8 (GND), U40.1 (VSS), U40.13 (GND), U41.3 (GND), U41.8 (GND), U42.3 (GND), U42.8 (GND), U43.1 (VSS), U43.13 (GND), U44.3 (GND), U44.8 (GND), U45.3 (GND), U45.8 (GND), U46.1 (VSS), U46.13 (GND), U47.3 (GND), U47.8 (GND), U48.3 (GND), U48.8 (GND), U49.1 (VSS), U49.13 (GND), U50.3 (GND), U50.8 (GND), U51.3 (GND), U51.8 (GND), U52.1 (VSS), U52.13 (GND), U53.3 (GND), U53.8 (GND), U54.3 (GND), U54.8 (GND), U55.1 (VSS), U55.13 (GND), U56.3 (GND), U56.8 (GND), U57.3 (GND), U57.8 (GND), U58.1 (VSS), U58.13 (GND), U59.3 (GND), U59.8 (GND), U60.3 (GND), U60.8 (GND), U61.1 (VSS), U61.13 (GND), U62.3 (GND), U62.8 (GND), U63.3 (GND), U63.8 (GND), U64.1 (VSS), U64.13 (GND), U65.3 (GND), U65.8 (GND), U66.3 (GND), U66.8 (GND), U67.1 (VSS), U67.13 (GND), U68.3 (GND), U68.8 (GND), U69.3 (GND), U69.8 (GND), U70.4 (GND), U71.4 (GND), U72.4 (GND), U73.4 (GND), U74.4 (GND), U75.4 (GND), U76.4 (GND), U77.4 (GND), U78.4 (GND), U79.4 (GND), U80.4 (GND), U81.4 (GND), U82.4 (GND), U83.4 (GND), U84.4 (GND), U85.4 (GND), U86.4 (GND), U87.4 (GND), U88.4 (GND), U89.4 (GND), U90.4 (GND), U91.4 (GND), U92.4 (GND), U93.4 (GND), U94.4 (GND), U95.4 (GND), U96.4 (GND), U97.4 (GND), U98.4 (GND), U99.4 (GND), U100.4 (GND), U101.4 (GND), U102.4 (GND), U103.4 (GND), U104.4 (GND), U105.4 (GND), U106.4 (GND), U107.4 (GND), U108.4 (GND), U109.4 (GND), U110.4 (GND), U111.4 (GND), U112.4 (GND), U113.4 (GND), U114.4 (GND), U115.4 (GND), U116.4 (GND), U117.4 (GND), U118.4 (GND), U119.4 (GND), U120.4 (GND), U121.4 (GND), U122.4 (GND), U123.4 (GND), U124.4 (GND), U125.4 (GND), U126.4 (GND), U127.4 (GND), U128.4 (GND), U129.4 (GND), U130.4 (GND), U131.4 (GND), U132.4 (GND), U133.4 (GND), U134.4 (GND), U135.4 (GND), U136.4 (GND), U137.4 (GND), U138.4 (GND), U139.4 (GND), U140.4 (GND), U141.4 (GND), U142.4 (GND), U143.4 (GND), U144.4 (GND), U145.4 (GND), U146.4 (GND), U147.4 (GND), U148.4 (GND), U149.4 (GND), U150.4 (GND), U151.4 (GND), U152.4 (GND), U153.4 (GND), Y1.2 (GND), Y1.4 (GND)
MUX_A0: U4.8 (PC0), U7.15 (A0), U10.15 (A0), U13.15 (A0), U16.15 (A0), U19.15 (A0), U22.15 (A0), U25.15 (A0), U28.15 (A0), U31.15 (A0), U34.15 (A0), U37.15 (A0), U40.15 (A0), U43.15 (A0), U46.15 (A0), U49.15 (A0), U52.15 (A0), U55.15 (A0), U58.15 (A0), U61.15 (A0), U64.15 (A0), U67.15 (A0)
MUX_A1: U4.9 (PC1), U7.14 (A1), U10.14 (A1), U13.14 (A1), U16.14 (A1), U19.14 (A1), U22.14 (A1), U25.14 (A1), U28.14 (A1), U31.14 (A1), U34.14 (A1), U37.14 (A1), U40.14 (A1), U43.14 (A1), U46.14 (A1), U49.14 (A1), U52.14 (A1), U55.14 (A1), U58.14 (A1), U61.14 (A1), U64.14 (A1), U67.14 (A1)
unnamed: J1.2, R1.1
unnamed: J1.3, R2.1
unnamed: LED1.1 (VDD), SC1.2
unnamed: LED2.1 (VDD), SC2.2
unnamed: LED3.1 (VDD), SC3.2
unnamed: LED4.1 (VDD), SC4.2
unnamed: LED5.1 (VDD), SC5.2
unnamed: LED6.1 (VDD), SC6.2
unnamed: LED7.1 (VDD), SC7.2
unnamed: LED8.1 (VDD), SC8.2
unnamed: LED9.1 (VDD), SC9.2
unnamed: LED10.1 (VDD), SC10.2
unnamed: LED11.1 (VDD), SC11.2
unnamed: LED12.1 (VDD), SC12.2
unnamed: LED13.1 (VDD), SC13.2
unnamed: LED14.1 (VDD), SC14.2
unnamed: LED15.1 (VDD), SC15.2
unnamed: LED16.1 (VDD), SC16.2
unnamed: LED17.1 (VDD), SC17.2
unnamed: LED18.1 (VDD), SC18.2
unnamed: LED19.1 (VDD), SC19.2
unnamed: LED20.1 (VDD), SC20.2
unnamed: LED21.1 (VDD), SC21.2
unnamed: LED22.1 (VDD), SC22.2
unnamed: LED23.1 (VDD), SC23.2
unnamed: LED24.1 (VDD), SC24.2
unnamed: LED25.1 (VDD), SC25.2
unnamed: LED26.1 (VDD), SC26.2
unnamed: LED27.1 (VDD), SC27.2
unnamed: LED28.1 (VDD), SC28.2
unnamed: LED29.1 (VDD), SC29.2
unnamed: LED30.1 (VDD), SC30.2
unnamed: LED31.1 (VDD), SC31.2
unnamed: LED32.1 (VDD), SC32.2
unnamed: LED33.1 (VDD), SC33.2
unnamed: LED34.1 (VDD), SC34.2
unnamed: LED35.1 (VDD), SC35.2
unnamed: LED36.1 (VDD), SC36.2
unnamed: LED37.1 (VDD), SC37.2
unnamed: LED38.1 (VDD), SC38.2
unnamed: LED39.1 (VDD), SC39.2
unnamed: LED40.1 (VDD), SC40.2
unnamed: LED41.1 (VDD), SC41.2
unnamed: LED42.1 (VDD), SC42.2
unnamed: LED43.1 (VDD), SC43.2
unnamed: LED44.1 (VDD), SC44.2
unnamed: LED45.1 (VDD), SC45.2
unnamed: LED46.1 (VDD), SC46.2
unnamed: LED47.1 (VDD), SC47.2
unnamed: LED48.1 (VDD), SC48.2
unnamed: LED49.1 (VDD), SC49.2
unnamed: LED50.1 (VDD), SC50.2
unnamed: LED51.1 (VDD), SC51.2
unnamed: LED52.1 (VDD), SC52.2
unnamed: LED53.1 (VDD), SC53.2
unnamed: LED54.1 (VDD), SC54.2
unnamed: LED55.1 (VDD), SC55.2
unnamed: LED56.1 (VDD), SC56.2
unnamed: LED57.1 (VDD), SC57.2
unnamed: LED58.1 (VDD), SC58.2
unnamed: LED59.1 (VDD), SC59.2
unnamed: LED60.1 (VDD), SC60.2
unnamed: LED61.1 (VDD), SC61.2
unnamed: LED62.1 (VDD), SC62.2
unnamed: LED63.1 (VDD), SC63.2
unnamed: LED64.1 (VDD), SC64.2
unnamed: LED65.1 (VDD), SC65.2
unnamed: LED66.1 (VDD), SC66.2
unnamed: LED67.1 (VDD), SC67.2
unnamed: LED68.1 (VDD), SC68.2
unnamed: LED69.1 (VDD), SC69.2
unnamed: LED70.1 (VDD), SC70.2
unnamed: LED71.1 (VDD), SC71.2
unnamed: LED72.1 (VDD), SC72.2
unnamed: LED73.1 (VDD), SC73.2
unnamed: LED74.1 (VDD), SC74.2
unnamed: LED75.1 (VDD), SC75.2
unnamed: LED76.1 (VDD), SC76.2
unnamed: LED77.1 (VDD), SC77.2
unnamed: LED78.1 (VDD), SC78.2
unnamed: LED79.1 (VDD), SC79.2
unnamed: LED80.1 (VDD), SC80.2
unnamed: LED81.1 (VDD), SC81.2
unnamed: LED82.1 (VDD), SC82.2
unnamed: LED83.1 (VDD), SC83.2
unnamed: LED84.1 (VDD), SC84.2
unnamed: R15.1, U3.3
unnamed: R35.2, U4.60 (BOOT0)
unnamed: C11.2, R34.1, U4.7 (NRST)
unnamed: C12.2, U4.5 (PH0), Y1.1
unnamed: C13.2, U4.6 (PH1), Y1.3
unnamed: C14.2, U4.31 (VCAP_1)
unnamed: C15.2, U4.47 (VCAP_2)
unnamed: C19.2, U5.14 (NR)
unnamed: C22.2, U6.14 (NR)

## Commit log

2025-12-27 feat: added symbol, footprint, and model for CT100
2025-12-27 docs: removed /datasheets in favor for direct urls
2025-12-28 feat: completed layout for a single switch
2026-03-20 feat: working changes
